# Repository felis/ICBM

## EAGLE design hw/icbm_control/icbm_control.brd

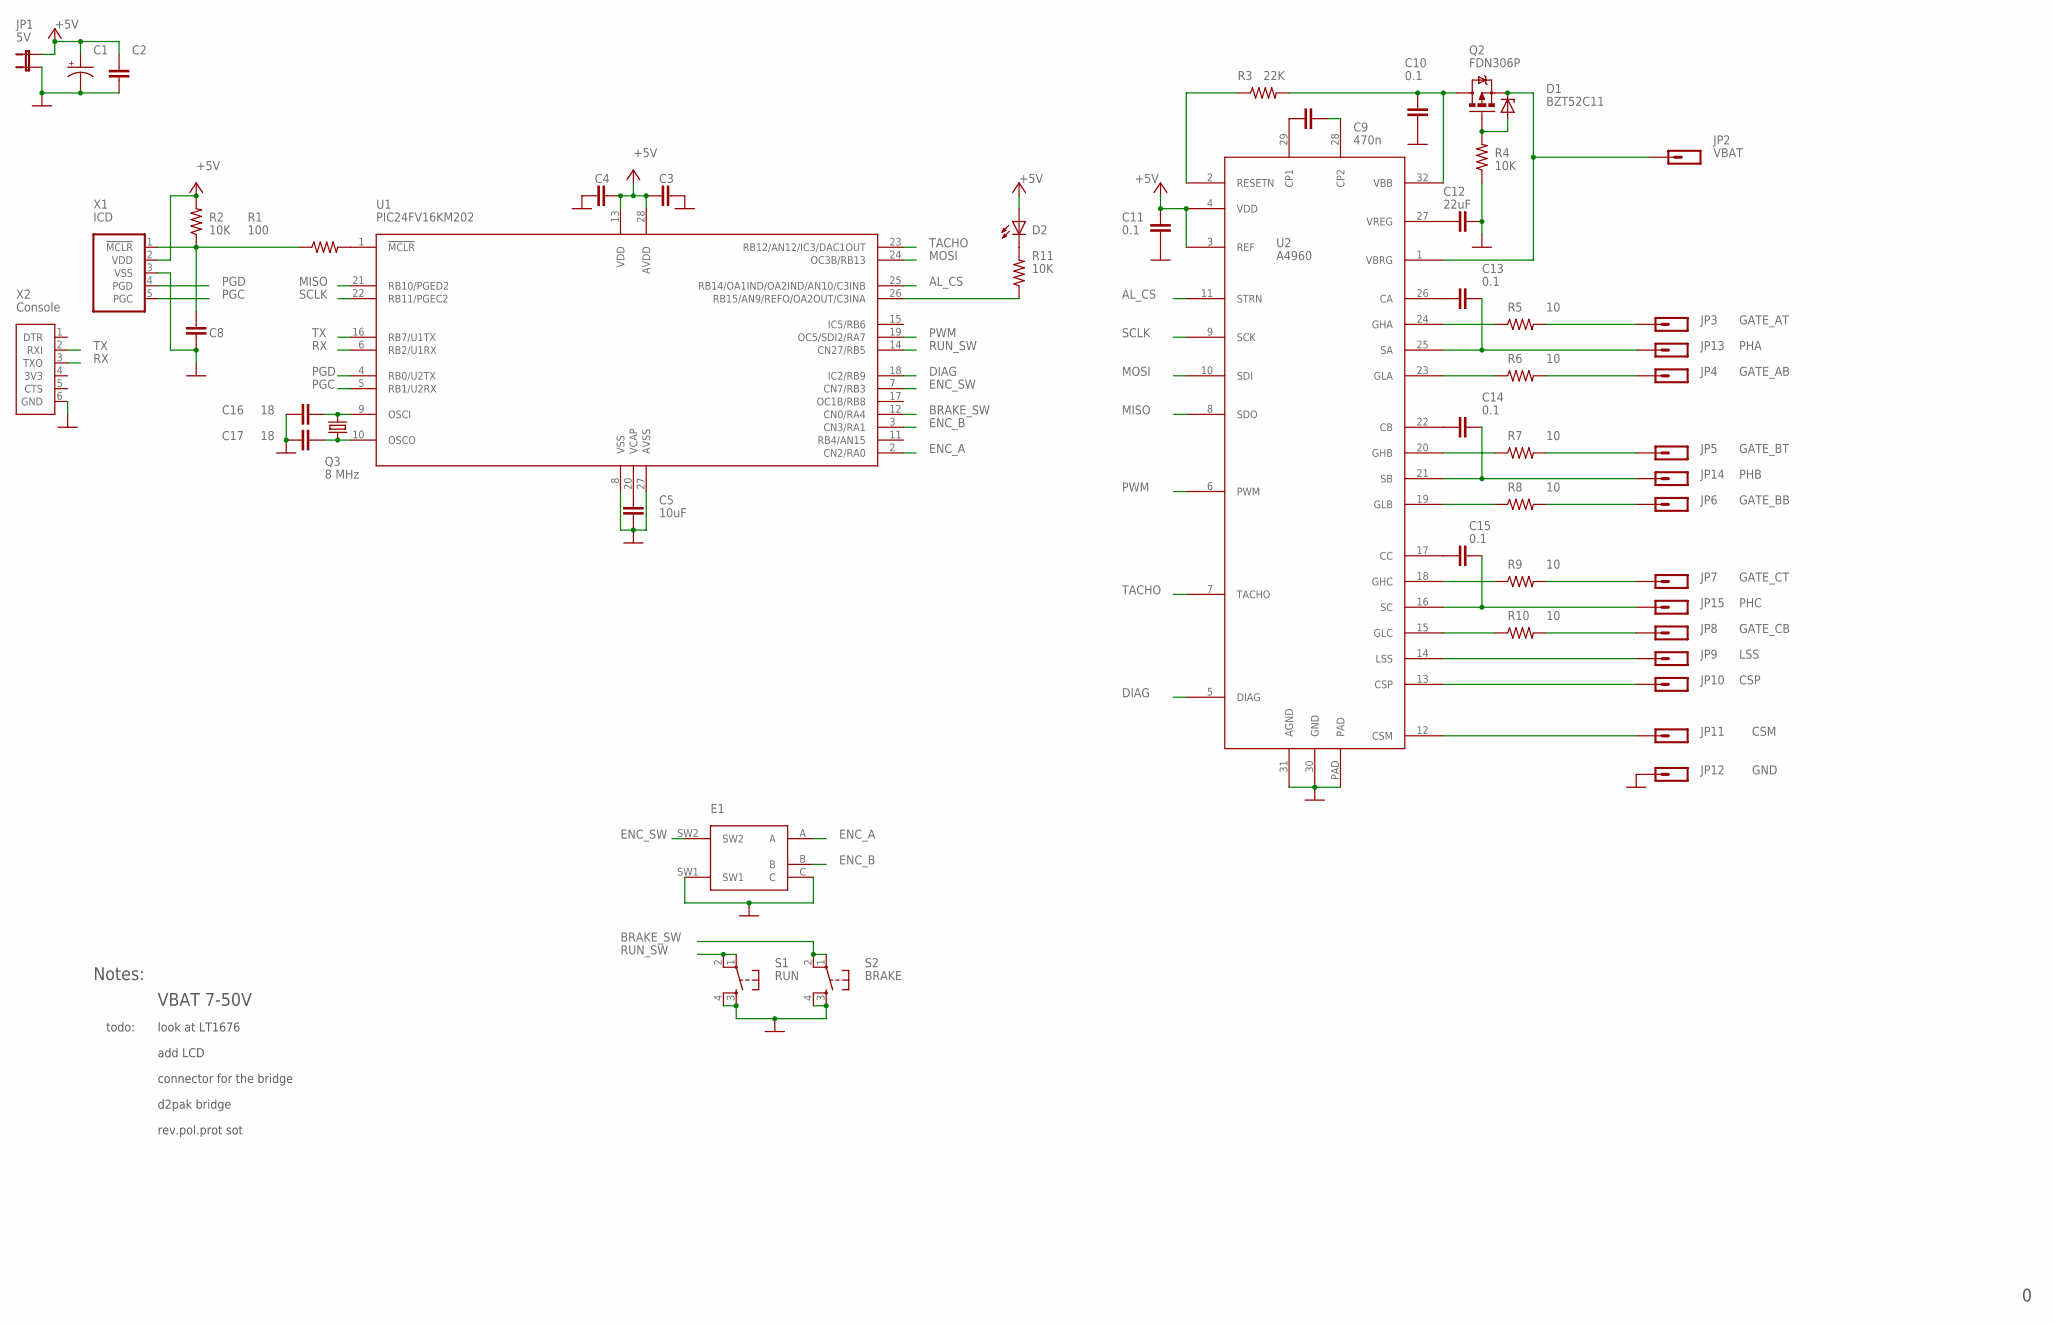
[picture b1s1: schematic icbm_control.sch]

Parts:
C1: CAP_POL-RAD8-TT; CAP_RAD_8MM_TT
C2: CAP0603; 0603
C3, C4, C8: 0.1uF; 0603
C5: 10uF; 0603
C9: 470n; 0603
C10, C11, C13, C14, C15: 0.1; 0603
C12: 22uF; 1206
C16, C17: 18; 0603
D1: BZT52C11; SOD-123
D2: LED-TT; LED5MM_TT
E1: ROTARY_ENCODER_SWITCH-LUT; PEC12-LUT
JP1: 5V; 1X02-LUT
JP2: VBAT; 1X01_TT
JP3: GATE_AT; 1X01_TT
JP4: GATE_AB; 1X01_TT
JP5: GATE_BT; 1X01_TT
JP6: GATE_BB; 1X01_TT
JP7: GATE_CT; 1X01_TT
JP8: GATE_CB; 1X01_TT
JP9: LSS; 1X01_TT
JP10: CSP; 1X01_TT
JP11: CSM; 1X01_TT
JP12: GND; 1X01_TT
JP13: PHA; 1X01_TT
JP14: PHB; 1X01_TT
JP15: PHC; 1X01_TT
Q2: FDN306P; DPAK
Q3: 8 MHz; HC49US_TT
R1: 100; 0603
R2, R4, R11: 10K; 0603
R3: 22K; 0603
R5, R6, R7, R8, R9, R10: 10; 0603
S1: RUN; TACT_PTH-LUT
S2: BRAKE; TACT_PTH-LUT
U1: PIC24FV16KM202; DIL28-3-TT
U2: A4960; LQPF-32
X1: ICD; 1X05-TT
X2: Console; 1X06TT

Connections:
+5V: C1.P (+), C2.1, C3.1, C4.2, C11.2, D2.A, JP1.2, R2.2, U1.13 (VDD), U1.28 (AVDD), U2.3 (REF), U2.4 (VDD), X1.2 (VDD)
AL_CS: U1.25 (RB14/OA1IND/OA2IND/AN10/C3INB), U2.11 (STRN)
BRAKE_SW: S2.1, S2.2, U1.12 (CN0/RA4)
CSM: JP11.1, U2.12 (CSM)
CSP: JP10.1, U2.13 (CSP)
DIAG: U1.18 (IC2/RB9), U2.5 (DIAG)
ENC_A: E1.A, U1.2 (CN2/RA0)
ENC_B: E1.B, U1.3 (CN3/RA1)
ENC_SW: E1.SW2, U1.7 (CN7/RB3)
GATE_AB: JP4.1, R6.2
GATE_AT: JP3.1, R5.2
GATE_BB: JP6.1, R8.2
GATE_BT: JP5.1, R7.2
GATE_CB: JP8.1, R10.2
GATE_CT: JP7.1, R9.2
GND: C1.N (-), C2.2, C3.2, C4.1, C5.2, C8.1, C10.1, C11.1, C12.2, C16.1, C17.1, E1.C, E1.SW1, JP1.1, JP12.1, R4.1, S1.3, S1.4, S2.3, S2.4, U1.8 (VSS), U1.27 (AVSS), U2.30 (GND), U2.31 (AGND), U2.PAD, X1.3 (VSS), X2.6 (GND)
LSS: JP9.1, U2.14 (LSS)
MISO: U1.21 (RB10/PGED2), U2.8 (SDO)
MOSI: U1.24 (OC3B/RB13), U2.10 (SDI)
unnamed: C5.1, U1.20 (VCAP)
unnamed: R1.2, U1.1 (!MCLR)
unnamed: R11.1, U1.26 (RB15/AN9/REFO/OA2OUT/C3INA)
unnamed: C9.1, U2.29 (CP1)
unnamed: D2.K (C), R11.2
unnamed: C9.2, U2.28 (CP2)
unnamed: C8.2, R1.1, R2.1, X1.1 (!MCLR)
unnamed: R3.1, U2.2 (RESETN)
unnamed: C10.2, Q2.4 (D), R3.2, U2.32 (VBB)
unnamed: C12.1, U2.27 (VREG)
unnamed: C13.2, U2.26 (CA)
unnamed: D1.A, Q2.1 (G), R4.2
unnamed: C14.2, U2.22 (CB)
unnamed: C15.2, U2.17 (CC)
unnamed: C13.1, JP13.1, U2.25 (SA)
unnamed: C14.1, JP14.1, U2.21 (SB)
unnamed: C15.1, JP15.1, U2.16 (SC)
unnamed: R5.1, U2.24 (GHA)
unnamed: R7.1, U2.20 (GHB)
unnamed: R9.1, U2.18 (GHC)
unnamed: R6.1, U2.23 (GLA)
unnamed: R8.1, U2.19 (GLB)
unnamed: R10.1, U2.15 (GLC)
unnamed: C16.2, Q3.2, U1.9 (OSCI)
unnamed: C17.2, Q3.1, U1.10 (OSCO)
PGC: U1.5 (RB1/U2RX), X1.5 (PGC)
PGD: U1.4 (RB0/U2TX), X1.4 (PGD)
PWM: U1.19 (OC5/SDI2/RA7), U2.6 (PWM)
RUN_SW: S1.1, S1.2, U1.14 (CN27/RB5)
RX: U1.6 (RB2/U1RX), X2.3 (TXO)
SCLK: U1.22 (RB11/PGEC2), U2.9 (SCK)
TACHO: U1.23 (RB12/AN12/IC3/DAC1OUT), U2.7 (TACHO)
TX: U1.16 (RB7/U1TX), X2.2 (RXI)
VBAT: D1.K (C), JP2.1, Q2.3 (S), U2.1 (VBRG)

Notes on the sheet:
Notes:
VBAT 7-50V
look at LT1676
todo:
add LCD
connector for the bridge
d2pak bridge
rev.pol.prot sot

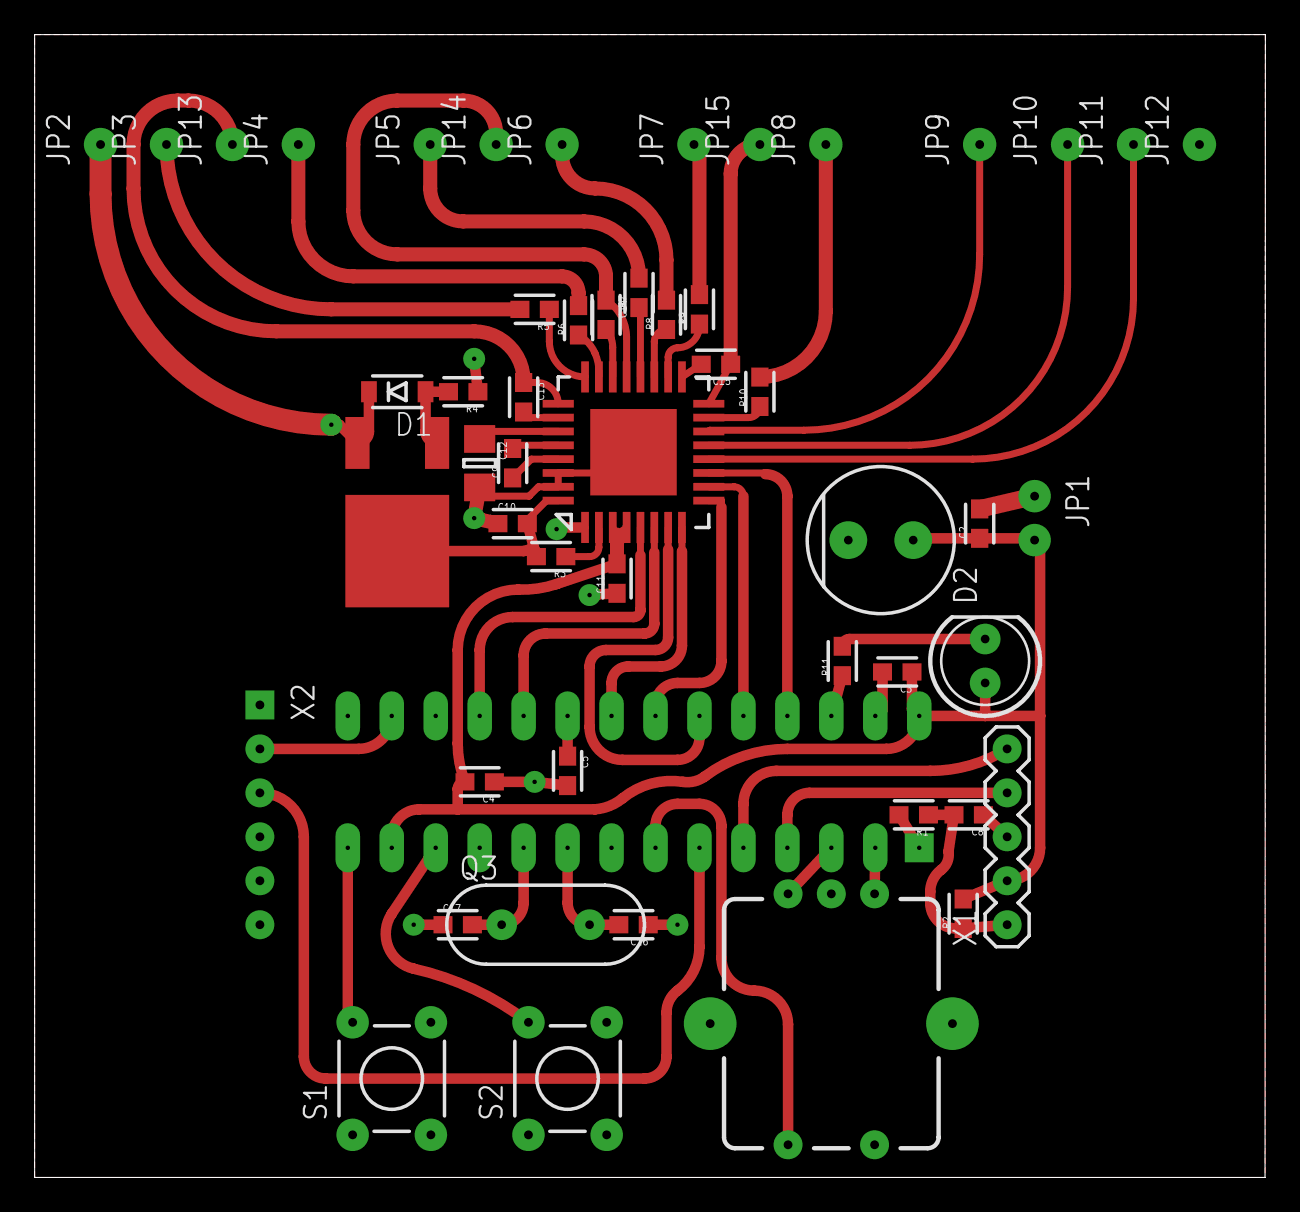
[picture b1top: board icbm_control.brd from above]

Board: 2 copper layers, 71.1 x 66.0 mm, 52 parts (1 on the bottom side), 53 nets.

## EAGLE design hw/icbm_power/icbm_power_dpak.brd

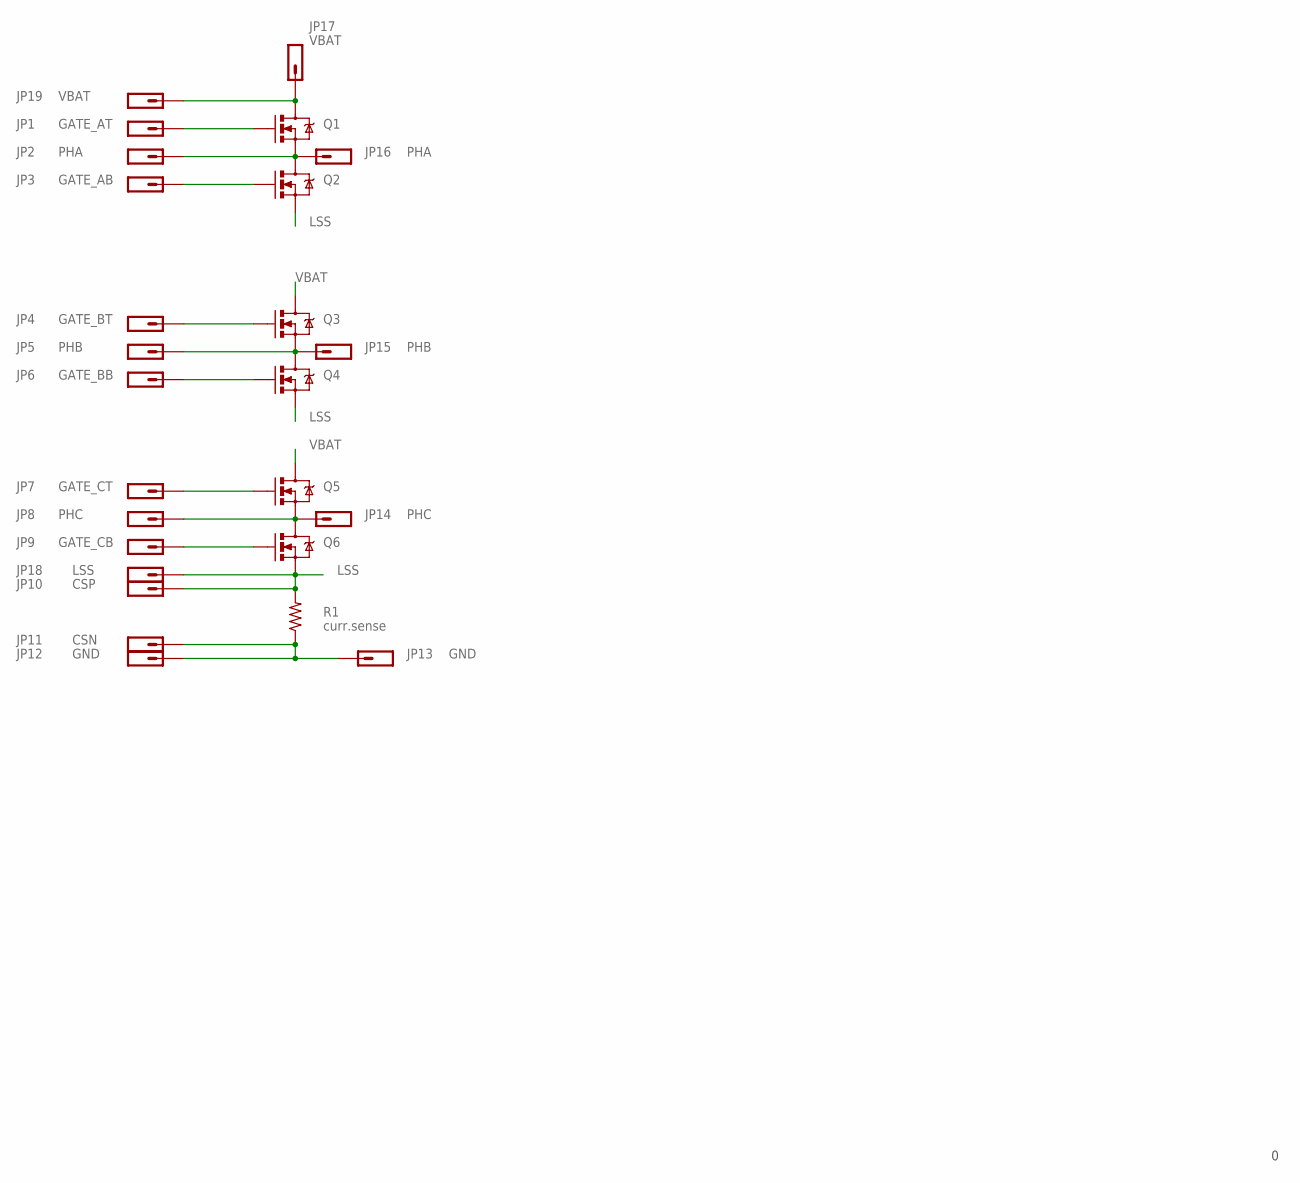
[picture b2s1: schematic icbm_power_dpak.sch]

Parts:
JP1: GATE_AT; 1X01_TT
JP2, JP16: PHA; 1X01_TT
JP3: GATE_AB; 1X01_TT
JP4: GATE_BT; 1X01_TT
JP5, JP15: PHB; 1X01_TT
JP6: GATE_BB; 1X01_TT
JP7: GATE_CT; 1X01_TT
JP8, JP14: PHC; 1X01_TT
JP9: GATE_CB; 1X01_TT
JP10: CSP; 1X01_TT
JP11: CSN; 1X01_TT
JP12, JP13: GND; 1X01_TT
JP17, JP19: VBAT; 1X01_TT
JP18: LSS; 1X01_TT
Q1, Q2, Q3, Q4, Q5, Q6: MOSFET-NCHANNEL-DPAK; DPAK
R1: curr.sense; 2512

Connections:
GND: JP11.1, JP12.1, JP13.1, R1.P$1 (1)
LSS: JP10.1, JP18.1, Q2.3 (S), Q4.3 (S), Q6.3 (S), R1.P$2 (2)
unnamed: JP2.1, JP16.1, Q1.3 (S), Q2.4 (D)
unnamed: JP5.1, JP15.1, Q3.3 (S), Q4.4 (D)
unnamed: JP8.1, JP14.1, Q5.3 (S), Q6.4 (D)
unnamed: JP1.1, Q1.1 (G)
unnamed: JP3.1, Q2.1 (G)
unnamed: JP4.1, Q3.1 (G)
unnamed: JP6.1, Q4.1 (G)
unnamed: JP7.1, Q5.1 (G)
unnamed: JP9.1, Q6.1 (G)
VBAT: JP17.1, JP19.1, Q1.4 (D), Q3.4 (D), Q5.4 (D)

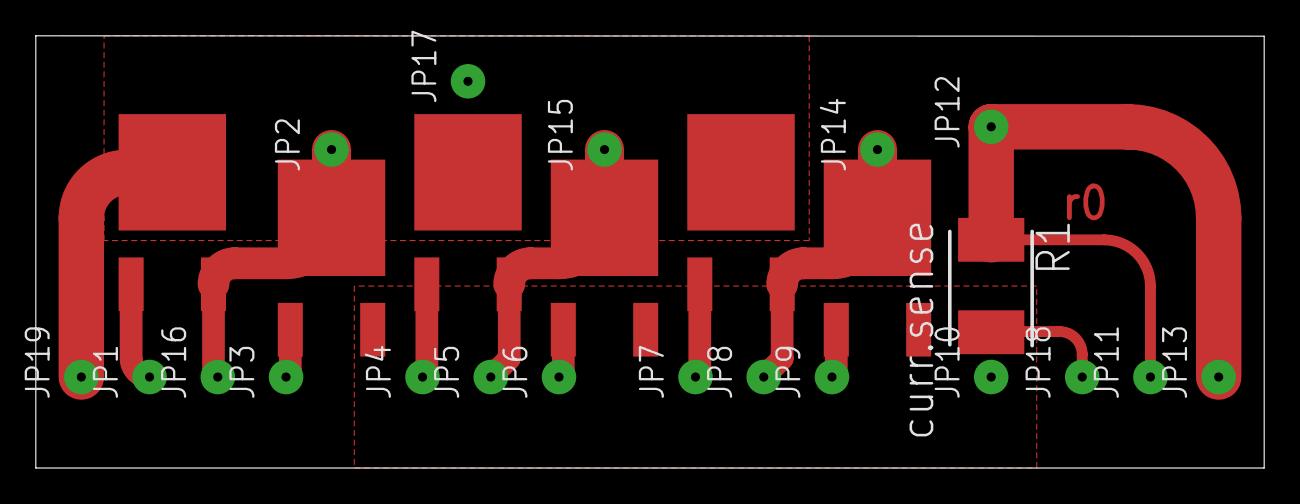
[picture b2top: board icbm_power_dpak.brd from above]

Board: 2 copper layers, 68.6 x 24.1 mm, 26 parts (0 on the bottom side), 12 nets.

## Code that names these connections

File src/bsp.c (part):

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
#define CONS_RX_TRIS _TRISB2    //console
#define MISO_TRIS _TRISB10      //SPI
#define TACHO_TRIS _TRISB12     //OC to measure length of tacho
#define DIAG_TRIS  _TRISB9      //DIAG input

#define RBUT_MASK     _PORTB_RB5_MASK
#define RBUT_TRIS     _TRISB5    //RUN button
#define RBUT_PIN      _RB5
#define RBUT_PULLUP   _CN27PUE

#define BBUT_MASK     _PORTA_RA4_MASK
#define BBUT_TRIS     _TRISA4    //BRAKE button
#define BBUT_PIN      _RA4
#define BBUT_PULLUP   _CN0PUE

#define EBUT_MASK     _PORTB_RB3_MASK
#define EBUT_TRIS     _TRISB3    //Button on encoder shaft
#define EBUT_PIN      _RB3
#define EBUT_PULLUP   _CN7PUE

//it pays to keep encoder channels together
#define ENCA_MASK     _PORTA_RA0_MASK
#define ENCA_TRIS     _TRISA0   //Encoder A channel
#define ENCA_PIN      _RA0
#define ENCA_PULLUP   _CN2PUE

#define ENCB_MASK     _PORTA_RA1_MASK
#define ENCB_TRIS     _TRISA1    //Encoder B channel
#define ENCB_PIN      _RA1
#define ENCB_PULLUP   _CN3PUE

#define ENC_PORT      PORTA
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
/* A4960 */

#define A4960_CS_PIN _RB14


#define TIMER1_ISR_PRIO         4
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
/*${BSP::PWM::PWM_init} ....................................................*/
static void PWM_init(void) {
    //_RA7 = 1;
    //return;

    CCP5CON1Lbits.CCSEL = 0;    //mode
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    CCP3CON1Lbits.TMRPS = 0;   //prescaler
    CCP3CON1Lbits.CCPON = 1;   //enable

    //_CCT3IP = 1;    //tacho timer interrupt priority
                    //must be lower than tacho capture
    _CCP3IP = 6;    //tacho capture interrupt priority
}
/*${BSP::BSP_init} .........................................................*/
void BSP_init(void) {
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    T1CONbits.TON = 1;                                     /* start Timer 1 */

    /* Enable peripheral interrupts as late as possible */
    //_CCT3IE = 1;    //tacho timer
    _CCP3IE = 1;    //tacho capture
    _U1RXIE = 1;                                     /* Console on UART1 Rx */
    _NVMIE = 1;            //EEPROM
}
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
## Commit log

2015-10-22 FIELD refactoring begin
2015-10-22 limits menu done
2015-10-22 hardware first commit
2015-10-23 run menu ref'd
2015-10-23 icbm pdf schematic added
2015-11-08 added lib backup to .gitignore
2015-11-08 oldie sync
2015-11-08 icbm_control mod
2015-11-09 added LED pin
2015-11-09 sync
2015-11-09 more to .gitignore
2015-11-09 LED Blinke added
2015-11-11 diag output added on status
2015-11-11 cosmetic
2015-11-22 rev0

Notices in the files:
src/bsp.c:
modify it under the terms of the GNU General Public License as published
